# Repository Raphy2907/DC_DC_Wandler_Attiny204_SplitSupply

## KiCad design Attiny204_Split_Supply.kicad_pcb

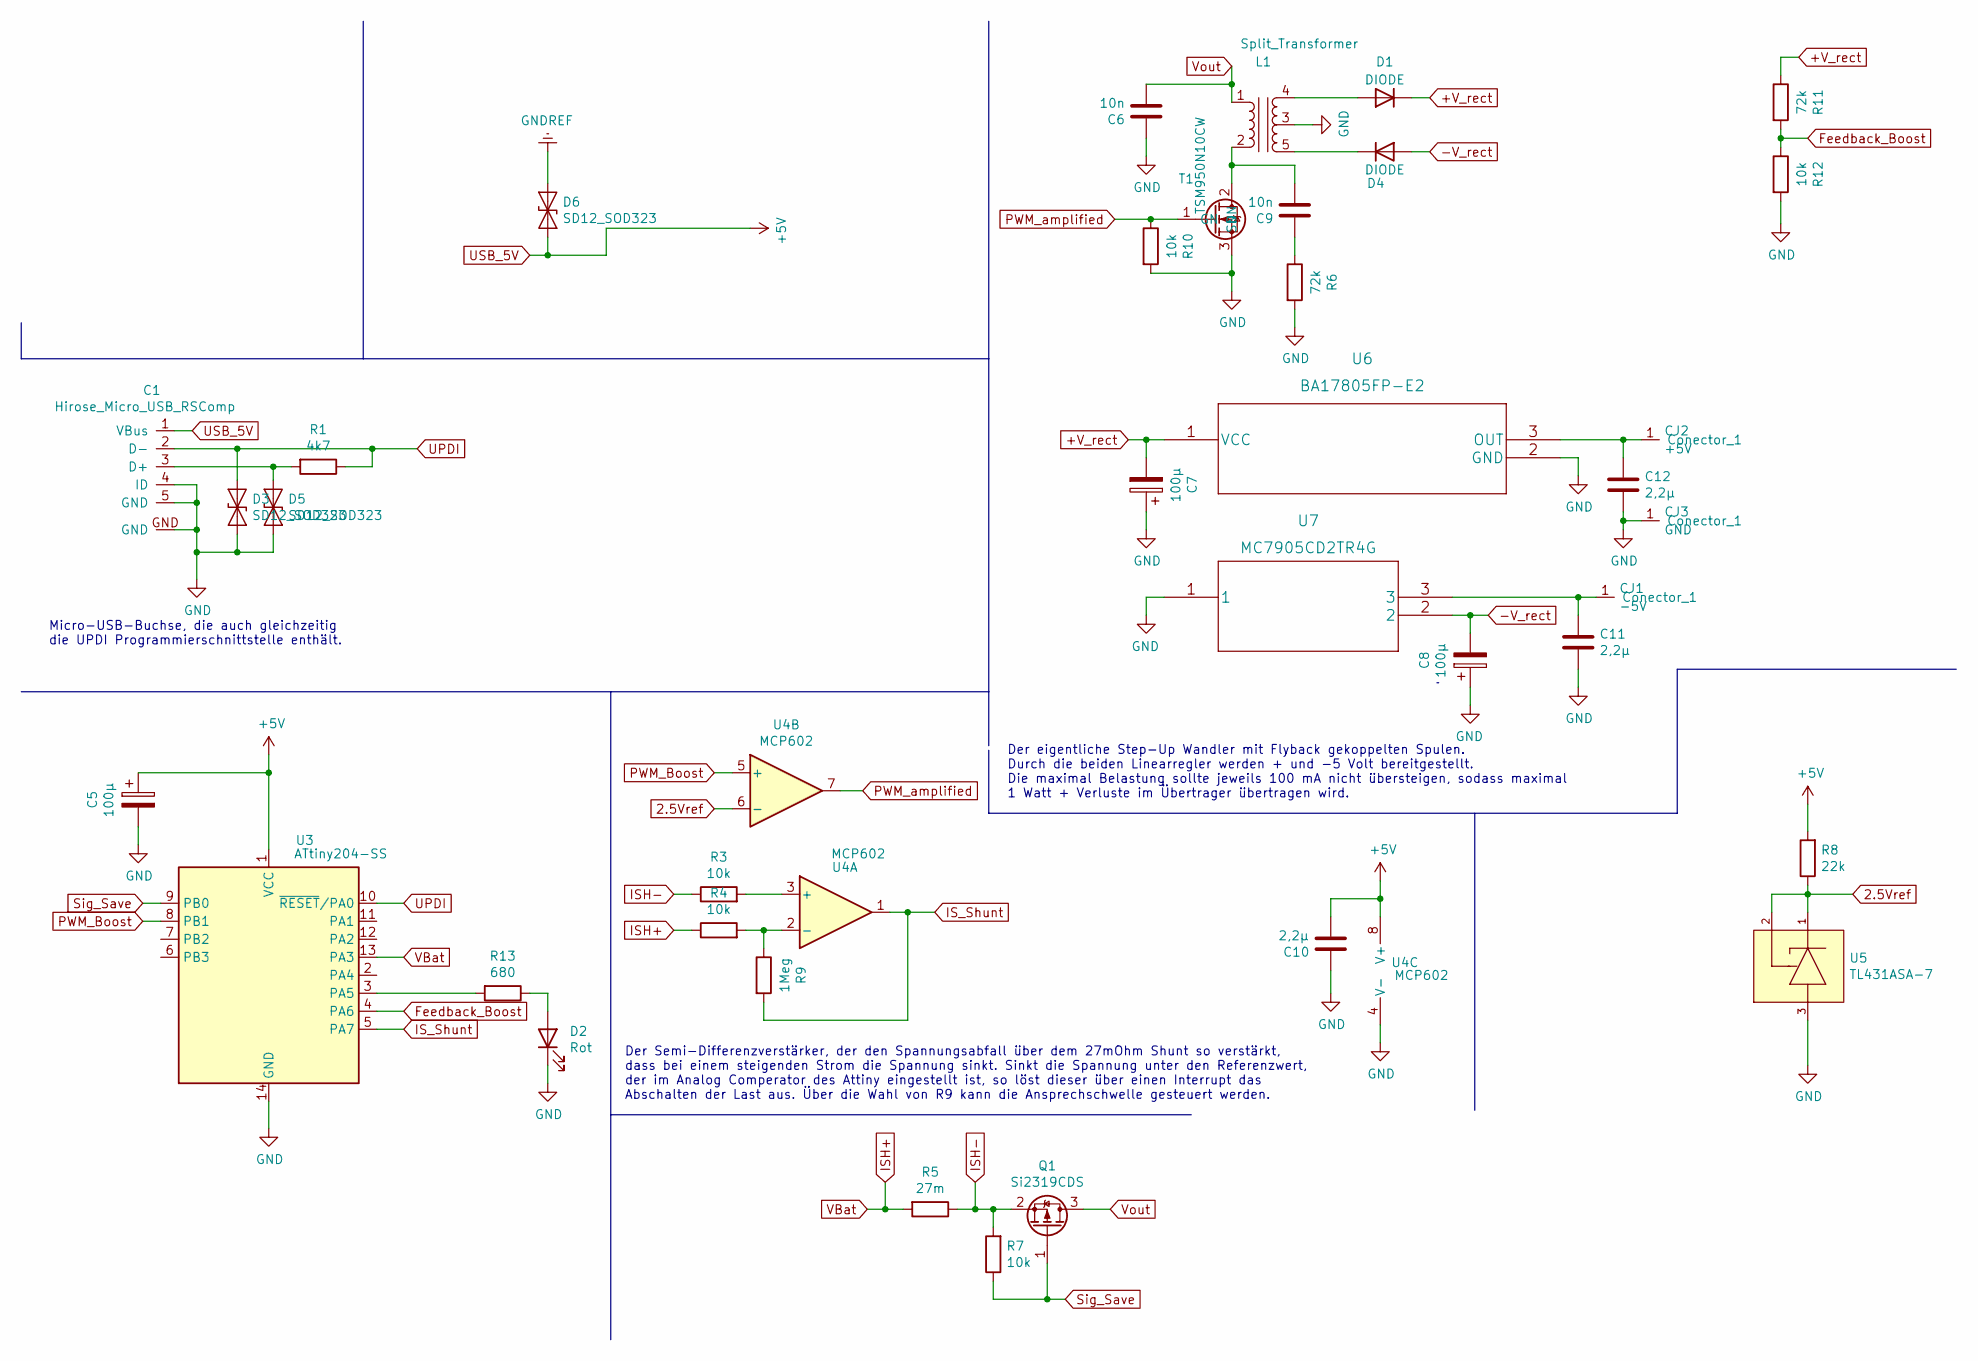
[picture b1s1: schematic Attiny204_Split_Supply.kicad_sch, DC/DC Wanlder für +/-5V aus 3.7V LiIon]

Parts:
C1: Hirose_Micro_USB_RSComp; USB_Micro_Hirose_RSComponents
C5, C7, C8: 100µ; CP_Elec_8x6.7
C6, C9: 10n; C_1206_3216Metric_Pad1.33x1.80mm_HandSolder
C10, C11, C12: 2,2µ; C_1206_3216Metric_Pad1.33x1.80mm_HandSolder
CJ1: -5V; 1_THT_Lötpad
CJ2: +5V; 1_THT_Lötpad
CJ3: GND; 1_THT_Lötpad
D1, D4: DIODE; D_SMA_Handsoldering
D2: Rot; 2_THT_Lötpads
D3, D5, D6: SD12_SOD323; D_0805_2012Metric_Pad1.15x1.40mm_HandSolder
L1: Split_Transformer; Split_Ferrit_Transformer
Q1: Si2319CDS; SOT-23
R1: 4k7; R_1206_3216Metric_Pad1.30x1.75mm_HandSolder
R3, R4, R7, R10, R12: 10k; R_1206_3216Metric_Pad1.30x1.75mm_HandSolder
R5: 27m; R_1206_3216Metric_Pad1.30x1.75mm_HandSolder
R6, R11: 72k; R_1206_3216Metric_Pad1.30x1.75mm_HandSolder
R8: 22k; R_1206_3216Metric_Pad1.30x1.75mm_HandSolder
R9: 1Meg; R_1206_3216Metric_Pad1.30x1.75mm_HandSolder
R13: 680; R_1206_3216Metric_Pad1.30x1.75mm_HandSolder
T1: TSM950N10CW; SOT-223-3_TabPin2
U3: ATtiny204-SS; SOIC-14_3.9x8.7mm_P1.27mm
U4: MCP602; SOIC-8_3.9x4.9mm_P1.27mm
U5: TL431ASA-7; SOT-23; mouser part number 621-TL431ASA-7; digikey description IC VREF SHUNT ADJ SOT23-3
U6: BA17805FP-E2; TO-252-2
U7: MC7905CD2TR4G

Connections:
2.5Vref: R8.1, U4.6 (-), U5.1 (CATHODE), U5.2 (REF)
+V_rect: C7.2, D1.2 (K), R11.1, U6.1 (VCC)
-V_rect: C8.2, D4.1 (A), U7.2
Feedback_Boost: R11.2, R12.1, U3.4 (PA6)
GND: C1.4 (ID), C1.5 (GND), C1.GND, C5.2, C6.1, C7.1, C8.1, C10.1, C11.2, C12.2, CJ3.1 (Conector_1), D2.1 (K), D3.2 (A2), D5.2 (A2), L1.3, R6.2, R10.2, R12.2, T1.3 (SN), U3.14 (GND), U4.4 (V-), U5.3 (ANODE), U6.2 (GND), U7.1
GNDREF: D6.1 (A1)
ISH+: R4.1, R5.2, U3.13 (PA3)
ISH-: Q1.2 (S), R3.1, R5.1, R7.2
IS_Shunt: R9.2, U3.5 (PA7), U4.1
unnamed: C1.3 (D+), D5.1 (A1), R1.2
unnamed: C9.1, R6.1
unnamed: C9.2, L1.2, T1.2 (DN)
unnamed: C11.1, CJ1.1 (Conector_1), U7.3
unnamed: C12.1, CJ2.1 (Conector_1), U6.3 (OUT)
unnamed: D1.1 (A), L1.4
unnamed: D2.2 (A), R13.1
unnamed: D4.2 (K), L1.5
unnamed: R3.2, U4.3 (+)
unnamed: R4.2, R9.1, U4.2 (-)
unnamed: R13.2, U3.3 (PA5)
PWM_Boost: U3.8 (PB1), U4.5 (+)
PWM_amplified: R10.1, T1.1 (GN), U4.7
Sig_Save: Q1.1 (G), R7.1, U3.9 (PB0)
UPDI: C1.2 (D-), D3.1 (A1), R1.1, U3.10 (~RESET/PA0)
USB_5V: C1.1 (VBus), C5.1, C10.2, D6.2 (A2), R8.2, U3.1 (VCC), U4.8 (V+)
Vout: C6.2, L1.1, Q1.3 (D)

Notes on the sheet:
Der eigentliche Step-Up Wandler mit Flyback gekoppelten Spulen. Durch die beiden Linearregler werden + und -5 Volt bereitgestellt. Die maximal Belastung sollte jeweils 100 mA nicht übersteigen, sodass maximal 1 Watt + Verluste im Übertrager übertragen wird.
Der Semi-Differenzverstärker, der den Spannungsabfall über dem 27mOhm Shunt so verstärkt, dass bei einem steigenden Strom die Spannung sinkt. Sinkt die Spannung unter den Referenzwert, der im Analog Comperator des Attiny eingestellt ist, so löst dieser über einen Interrupt das Abschalten der Last a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
Micro-USB-Buchse, die auch gleichzeitig die UPDI Programmierschnittstelle enthält.

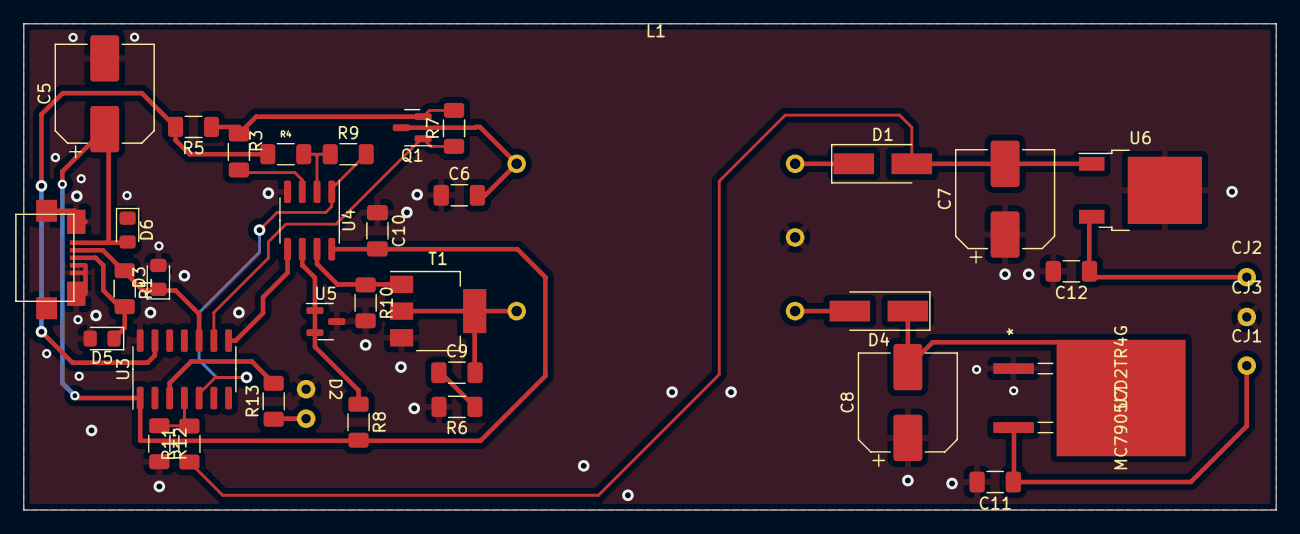
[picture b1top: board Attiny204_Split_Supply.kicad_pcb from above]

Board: 2 copper layers, 107.9 x 41.9 mm, 38 parts (0 on the bottom side), 25 nets.

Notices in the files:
parts and their libraries:
Copyright 2021 Accelerated Designs. All rights reserved.
